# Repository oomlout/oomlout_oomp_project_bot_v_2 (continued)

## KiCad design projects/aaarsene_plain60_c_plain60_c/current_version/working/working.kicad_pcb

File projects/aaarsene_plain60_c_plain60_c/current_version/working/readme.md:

# plain60_c
 
## summary 
* id: aaarsene_plain60_c_plain60_c
* user: aaarsene
* name: plain60_c
* board: plain60_c
* repo: https://github.com/aaarsene/plain60-c
* src_file_repo_kicad_pcb: plain60-c.kicad_pcb
* src_file_repo_kicad_pcb_link: https://github.com/aaarsene/plain60-c/tree/master/plain60-c.kicad_pcb
* src_file_repo_kicad_sch: plain60-c.kicad_sch
* src_file_repo_kicad_sch_link: https://github.com/aaarsene/plain60-c/tree/master/plain60-c.kicad_sch

* src_file_repo_sch: 
* src_file_repo_sch_link: https://github.com/aaarsene/plain60-c/tree/master/
* full details link: https://github.com/oomlout/oomlout_oomp_project_bot_v_2/tree/main/projects/aaarsene_plain60_c_plain60_c/current_version/working  

## schematic  
  
[schematic (pdf)](working_schematic.pdf) 

## pcb  

[board (pdf)](working.pdf)  

## working_bom
| Id | Designator | Footprint | Quantity | Designation | Supplier and ref |  | None | 
| --- | --- | --- | --- | --- | --- | --- | --- | 
| 1 | K19,K20,K23,K24,K17,K22,K21,K18,K8,K10,K14,K5,K13,K12,K11,K9,K7,K6,K4,K2,K1,K3,K62-1,K53,K57,K54,K56,K52,K55,K15-1,K28,K48,K25,K36,K33,K59,K39,K27,K50,K34,K47,K43,K38,K35,K32,K40,K42,K41,K26,K37,K51,K73-1,K49 | CHERRY_PLATE_100H | 53 | KEYSW |  |  | [''] | 
| 2 | K16,K61-1,K29,K63-1,K72-1,K74-1 | CHERRY_PLATE_150H | 6 | KEYSW |  |  | [''] | 
| 3 | K15 | CHERRY_PCB_200H | 1 | KEYSW |  |  | [''] | 
| 4 | K71,K31-1,K46-1,K74,K73,K63,K72,K61,K62 | CHERRY_PLATE_125H | 9 | KEYSW |  |  | [''] | 
| 5 | K58-1,K31 | CHERRY_PLATE_175H | 2 | KEYSW |  |  | [''] | 
| 6 | K44,K46 | CHERRY_PCB_225H | 2 | KEYSW |  |  | [''] | 
| 7 | S4,S5 | 10x5_7x2.5mm | 2 | Screw |  |  | [''] | 
| 8 | K58 | CHERRY_PCB_275H | 1 | KEYSW |  |  | [''] | 
| 9 | K67 | CHERRY_PCB_625H_F | 1 | KEYSW |  |  | [''] | 
| 10 | S8,S7,S9 | 5.5_5x2.5mm | 3 | Tofu screw |  |  | [''] | 
| 11 | S2,S1,S3,S6 | 5.5_5x2.5mm | 4 | Screw |  |  | [''] | 
| 12 | K67-1 | CHERRY_PCB_700H_F | 1 | KEYSW |  |  | [''] | 
| 13 | K44-1 | CHERRY_PCB_200H_V | 1 | KEYSW |  |  | [''] | 
| 14 | D73,D72,D71,D67,D63,D59,D58,D57,D56,D53,D51,D50,D27,D42,D18,D25,D41,D36,D31,D40,D37,D32,D34,D21,D26,D22,D24,D43,D38,D35,D48,D54,D44,D62,D39,D20,D28,D33,D23,D55,D52,D19,D10,D14,D9,D13,D11,D15,D17,D16,D12,D7,D3,D5,D8,D6,D4,D74,D49,D46,D29,D1,D47,D2,D61 | D_0805 | 65 | D |  |  | [''] | 
| 15 | U1 | ATMEGA32U4 | 1 | ATmega32U4 |  |  | [''] | 
| 16 | X1 | Resonator_SMD_muRata_CSTNExxV-3Pin-p1.2 | 1 | XTAL_GND |  |  | [''] | 
| 17 | SW1 | SW_SPST_TL3342 | 1 | SW_PUSH |  |  | [''] | 
| 18 | R6,R5 | R_0805 | 2 | 10k |  |  | [''] | 
| 19 | G*** | oshw | 1 | LOGO |  |  | [''] | 
| 20 | H4 | free_pin | 1 | +5v |  |  | [''] | 
| 21 | H1 | free_pin | 1 | B0 |  |  | [''] | 
| 22 | R1,R2 | R_0805 | 2 | 22 |  |  | [''] | 
| 23 | J1 | HRO-TYPE-C-31-M-12 | 1 | HRO-TYPE-C-31-M-12 |  |  | [''] | 
| 24 | C4,C5,C2,C3 | C_0805 | 4 | 0.1u |  |  | [''] | 
| 25 | F1 | R_0805 | 1 | Polyfuse |  |  | [''] | 
| 26 | C1 | C_0805 | 1 | 1u |  |  | [''] | 
| 27 | R4,R3 | R_0805 | 2 | 5.1k |  |  | [''] | 
| 28 | U2 | USBLC6-2SC6 | 1 | USBLC6-2SC6 |  |  | [''] | 
| 29 | H3 | free_pin | 1 | GND |  |  | [''] | 
| 30 | J2 | isp_standard | 1 | ISP |  |  | [''] | 
| 31 | G*** | logo_new | 1 | LOGO |  |  | [''] | 
| 32 | J3 | JST_SH_SM04B-SRSS-TB_1x04-1MP_P1.00mm_Horizontal | 1 | ai03_ud |  |  | [''] | 
| 33 | LS1 | speaker_AST1109MLTRQ | 1 | Speaker |  |  | [''] | 
| 34 | C6 | C_0805 | 1 | 4.7u |  |  | [''] | 

## bom_schematic
| Ref | Qnty | Value | Cmp name | Footprint | Description | Vendor | DNP | 
| --- | --- | --- | --- | --- | --- | --- | --- | 
| C1 | 1 | 1u | C | Keeb_components:C_0805 | Unpolarized capacitor |  |  | 
| C2, C3, C4, C5 | 4 | 0.1u | C | Keeb_components:C_0805 | Unpolarized capacitor |  |  | 
| C6 | 1 | 4.7u | C | Keeb_components:C_0805 | Unpolarized capacitor |  |  | 
| D1, D2, D3, D4, D5, D6, D7, D8, D9, D10, D11, D12, D13, D14, D15, D16, D17, D18, D19, D20, D21, D22, D23, D24, D25, D26, D27, D28, D29, D31, D32, D33, D34, D35, D36, D37, D38, D39, D40, D41, D42, D43, D44, D46, D47, D48, D49, D50, D51, D52, D53, D54, D55, D56, D57, D58, D59, D61, D62, D63, D67, D71, D72, D73, D74 | 65 | D | D | Keeb_components:D_0805 | Diode |  |  | 
| F1 | 1 | Polyfuse | Polyfuse | Keeb_components:R_0805 | Resettable fuse, polymeric positive temperature coefficient |  |  | 
| H1 | 1 | B0 | Conn_01x01 | footprints:free_pin | Generic connector, single row, 01x01, script generated (kicad-library-utils/schlib/autogen/connector/) |  |  | 
| H3 | 1 | GND | Conn_01x01 | footprints:free_pin | Generic connector, single row, 01x01, script generated (kicad-library-utils/schlib/autogen/connector/) |  |  | 
| H4 | 1 | +5v | Conn_01x01 | footprints:free_pin | Generic connector, single row, 01x01, script generated (kicad-library-utils/schlib/autogen/connector/) |  |  | 
| J1 | 1 | HRO-TYPE-C-31-M-12 | HRO-TYPE-C-31-M-12 | Keeb_components:HRO-TYPE-C-31-M-12 |  |  |  | 
| J2 | 1 | ISP | Conn_02x03_Odd_Even | Keeb_components:isp_standard | Generic connector, double row, 02x03, odd/even pin numbering scheme (row 1 odd numbers, row 2 even numbers), script generated (kicad-library-utils/schlib/autogen/connector/) |  |  | 
| J3 | 1 | ai03_ud | Conn_01x04 | Keeb_components:JST_SH_SM04B-SRSS-TB_1x04-1MP_P1.00mm_Horizontal | Generic connector, single row, 01x04, script generated (kicad-library-utils/schlib/autogen/connector/) |  |  | 
| K1, K2, K3, K4, K5, K6, K7, K8, K9, K10, K11, K12, K13, K14, K17, K18, K19, K20, K21, K22, K23, K24, K25, K26, K27, K28, K32, K33, K34, K35, K36, K37, K38, K39, K40, K41, K42, K43, K47, K48, K49, K50, K51, K52, K53, K54, K55, K56, K57, K59 | 50 | KEYSW | KEYSW | Keeb_switches:CHERRY_PLATE_100H |  |  |  | 
| K15 | 1 | KEYSW | KEYSW | Keeb_switches:CHERRY_PCB_200H |  |  |  | 
| K15-1 | 1 | KEYSW | KEYSW | Keeb_switches:CHERRY_PLATE_100H |  |  |  | 
| K16, K29 | 2 | KEYSW | KEYSW | Keeb_switches:CHERRY_PLATE_150H |  |  |  | 
| K31 | 1 | KEYSW | KEYSW | Keeb_switches:CHERRY_PLATE_175H |  |  |  | 
| K31-1 | 1 | KEYSW | KEYSW | Keeb_switches:CHERRY_PLATE_125H |  |  |  | 
| K44, K46 | 2 | KEYSW | KEYSW | Keeb_switches:CHERRY_PCB_225H |  |  |  | 
| K44-1 | 1 | KEYSW | KEYSW | Keeb_switches:CHERRY_PCB_200H_V |  |  |  | 
| K46-1 | 1 | KEYSW | KEYSW | Keeb_switches:CHERRY_PLATE_125H |  |  |  | 
| K58 | 1 | KEYSW | KEYSW | Keeb_switches:CHERRY_PCB_275H |  |  |  | 
| K58-1 | 1 | KEYSW | KEYSW | Keeb_switches:CHERRY_PLATE_175H |  |  |  | 
| K61, K62, K63, K71, K72, K73, K74 | 7 | KEYSW | KEYSW | Keeb_switches:CHERRY_PLATE_125H |  |  |  | 
| K61-1 | 1 | KEYSW | KEYSW | Keeb_switches:CHERRY_PLATE_150H |  |  |  | 
| K62-1 | 1 | KEYSW | KEYSW | Keeb_switches:CHERRY_PLATE_100H |  |  |  | 
| K63-1 | 1 | KEYSW | KEYSW | Keeb_switches:CHERRY_PLATE_150H |  |  |  | 
| K67 | 1 | KEYSW | KEYSW | Keeb_switches:CHERRY_PCB_625H_F |  |  |  | 
| K67-1 | 1 | KEYSW | KEYSW | Keeb_switches:CHERRY_PCB_700H_F |  |  |  | 
| K72-1 | 1 | KEYSW | KEYSW | Keeb_switches:CHERRY_PLATE_150H |  |  |  | 
| K73-1 | 1 | KEYSW | KEYSW | Keeb_switches:CHERRY_PLATE_100H |  |  |  | 
| K74-1 | 1 | KEYSW | KEYSW | Keeb_switches:CHERRY_PLATE_150H |  |  |  | 
| LS1 | 1 | Speaker | Speaker | Keeb_components:speaker_AST1109MLTRQ | Speaker |  |  | 
| R1, R2 | 2 | 22 | R | Keeb_components:R_0805 | Resistor |  |  | 
| R3, R4 | 2 | 5.1k | R | Keeb_components:R_0805 | Resistor |  |  | 
| R5, R6 | 2 | 10k | R | Keeb_components:R_0805 | Resistor |  |  | 
| S1, S2, S3, S6 | 4 | Screw | Screw_Terminal_01x01 | footprints:5.5_5x2.5mm | Generic screw terminal, single row, 01x01, script generated (kicad-library-utils/schlib/autogen/connector/) |  |  | 
| S4, S5 | 2 | Screw | Screw_Terminal_01x01 | footprints:10x5_7x2.5mm | Generic screw terminal, single row, 01x01, script generated (kicad-library-utils/schlib/autogen/connector/) |  |  | 
| S7, S8, S9 | 3 | Tofu screw | Screw_Terminal_01x01 | footprints:5.5_5x2.5mm | Generic screw terminal, single row, 01x01, script generated (kicad-library-utils/schlib/autogen/connector/) |  |  | 
| SW1 | 1 | SW_PUSH | SW_PUSH | Button_Switch_SMD:SW_SPST_TL3342 |  |  |  | 
| U1 | 1 | ATmega32U4 | ATmega32U4 | Keeb_components:ATMEGA32U4 |  |  |  | 
| U2 | 1 | USBLC6-2SC6 | USBLC6-2SC6 | Keeb_components:USBLC6-2SC6 |  |  |  | 
| X1 | 1 | XTAL_GND | XTAL_GND | Keeb_components:Resonator_SMD_muRata_CSTNExxV-3Pin-p1.2 |  |  |  |

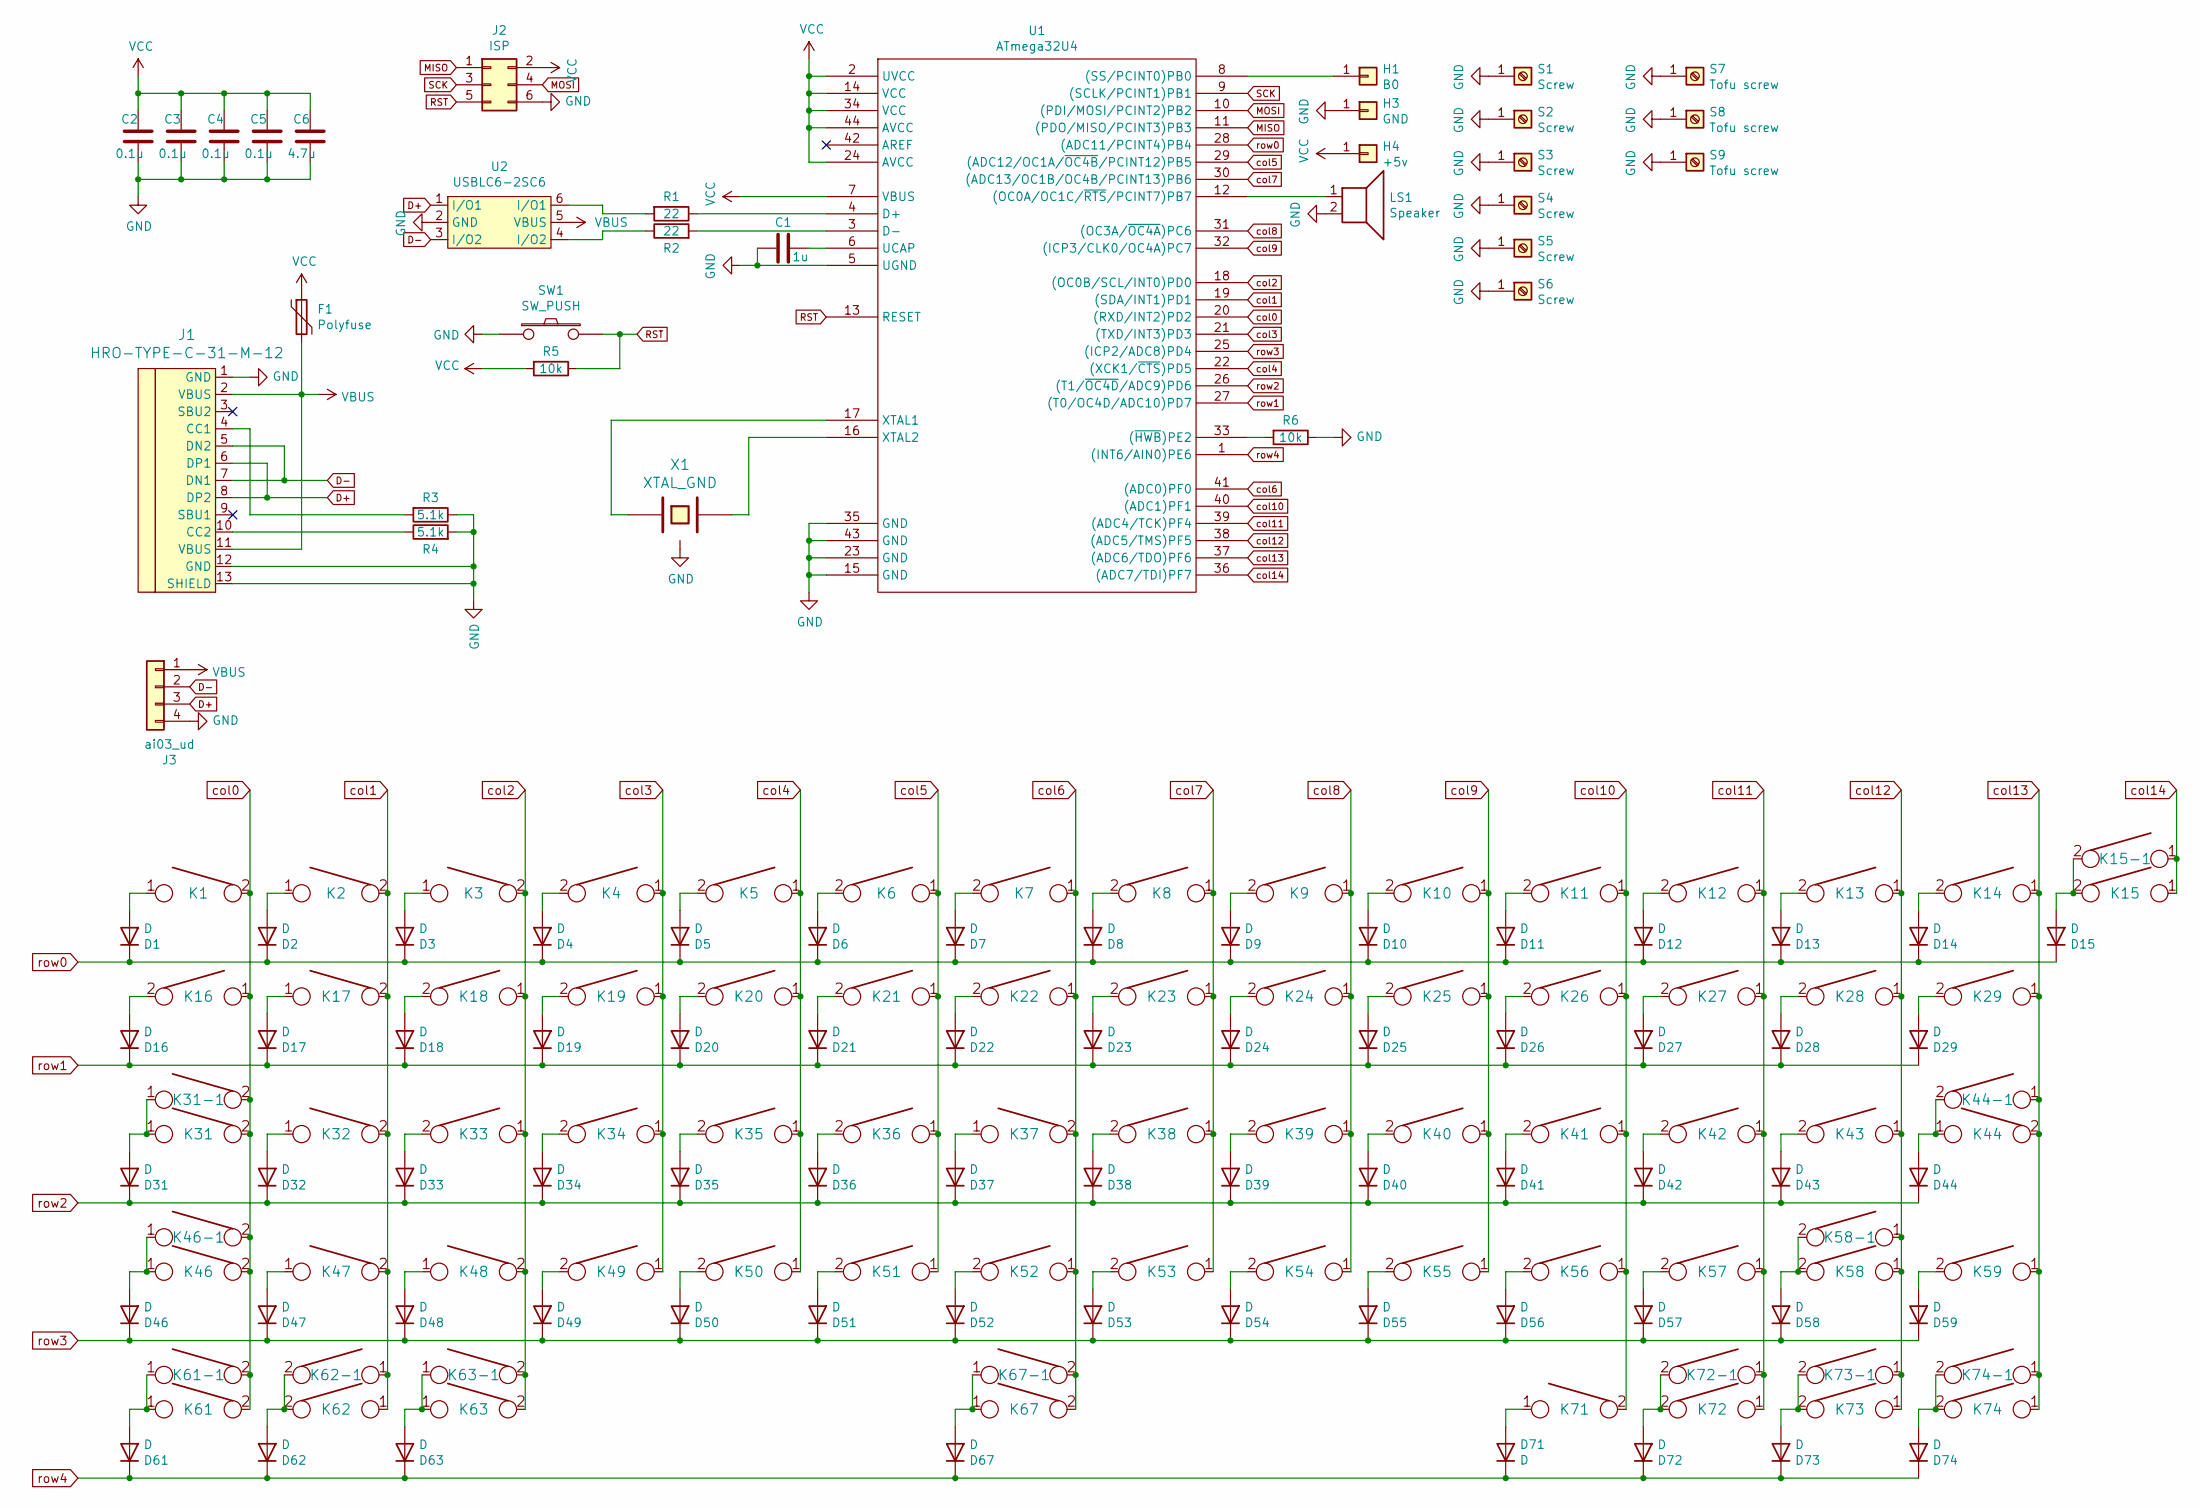
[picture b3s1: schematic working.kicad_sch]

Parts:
C1: 1u; C_0805
C2, C3, C4, C5: 0.1u; C_0805
C6: 4.7u; C_0805
D1, D2, D3, D4, D5, D6, D7, D8, D9, D10, D11, D12, D13, D14, D15, D16, D17, D18, D19, D20, D21, D22, D23, D24, D25, D26, D27, D28, D29, D31, D32, D33, D34, D35, D36, D37, D38, D39, D40, D41, D42, D43, D44, D46, D47, D48, D49, D50, D51, D52, D53, D54, D55, D56, D57, D58, D59, D61, D62, D63, D67, D71, D72, D73, D74: D; D_0805
F1: Polyfuse; R_0805
H1: B0; free_pin
H3: GND; free_pin
H4: +5v; free_pin
J1: HRO-TYPE-C-31-M-12
J2: ISP; isp_standard
J3: ai03_ud; JST_SH_SM04B-SRSS-TB_1x04-1MP_P1.00mm_Horizontal
K1, K2, K3, K4, K5, K6, K7, K8, K9, K10, K11, K12, K13, K14, K15-1, K17, K18, K19, K20, K21, K22, K23, K24, K25, K26, K27, K28, K32, K33, K34, K35, K36, K37, K38, K39, K40, K41, K42, K43, K47, K48, K49, K50, K51, K52, K53, K54, K55, K56, K57, K59, K62-1, K73-1: KEYSW; CHERRY_PLATE_100H
K15: KEYSW; CHERRY_PCB_200H
K16, K29, K61-1, K63-1, K72-1, K74-1: KEYSW; CHERRY_PLATE_150H
K31, K58-1: KEYSW; CHERRY_PLATE_175H
K31-1, K46-1, K61, K62, K63, K71, K72, K73, K74: KEYSW; CHERRY_PLATE_125H
K44, K46: KEYSW; CHERRY_PCB_225H
K44-1: KEYSW; CHERRY_PCB_200H_V
K58: KEYSW; CHERRY_PCB_275H
K67: KEYSW; CHERRY_PCB_625H_F
K67-1: KEYSW; CHERRY_PCB_700H_F
LS1: Speaker; speaker_AST1109MLTRQ
R1, R2: 22; R_0805
R3, R4: 5.1k; R_0805
R5, R6: 10k; R_0805
S1, S2, S3, S6: Screw; 5.5_5x2.5mm
S4, S5: Screw; 10x5_7x2.5mm
S7, S8, S9: Tofu screw; 5.5_5x2.5mm
SW1: SW_PUSH; SW_SPST_TL3342
U1: ATmega32U4; ATMEGA32U4
U2: USBLC6-2SC6; Farnell 1295310
X1: XTAL_GND; Resonator_SMD_muRata_CSTNExxV-3Pin-p1.2

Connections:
D+: J1.6 (DP1), J1.8 (DP2), J3.3, U2.1 (I/O1)
D-: J1.5 (DN2), J1.7 (DN1), J3.2, U2.3 (I/O2)
GND: C1.2, C2.1, C3.1, C4.1, C5.1, C6.1, H3.1, J1.1 (GND), J1.12 (GND), J1.13 (SHIELD), J2.6, J3.4, LS1.2, R3.1, R4.2, R6.1, S1.1, S2.1, S3.1, S4.1, S5.1, S6.1, S7.1, S8.1, S9.1, SW1.1, U1.5 (UGND), U1.15 (GND), U1.23 (GND), U1.35 (GND), U1.43 (GND), U2.2 (GND), X1.3
MISO: J2.1, U1.11 ((PDO/MISO/PCINT3)PB3)
MOSI: J2.4, U1.10 ((PDI/MOSI/PCINT2)PB2)
unnamed: C1.1, U1.6 (UCAP)
unnamed: D1.2 (A), K1.1
unnamed: D2.2 (A), K2.1
unnamed: D3.2 (A), K3.1
unnamed: D4.2 (A), K4.2
unnamed: D5.2 (A), K5.2
unnamed: D6.2 (A), K6.2
unnamed: D7.2 (A), K7.2
unnamed: D8.2 (A), K8.2
unnamed: D9.2 (A), K9.2
unnamed: D10.2 (A), K10.2
unnamed: D11.2 (A), K11.2
unnamed: D12.2 (A), K12.2
unnamed: D13.2 (A), K13.2
unnamed: D14.2 (A), K14.2
unnamed: D15.2 (A), K15.2, K15-1.2
unnamed: D16.2 (A), K16.2
unnamed: D17.2 (A), K17.1
unnamed: D18.2 (A), K18.2
unnamed: D19.2 (A), K19.2
unnamed: D20.2 (A), K20.2
unnamed: D21.2 (A), K21.2
unnamed: D22.2 (A), K22.2
unnamed: D23.2 (A), K23.2
unnamed: D24.2 (A), K24.2
unnamed: D25.2 (A), K25.2
unnamed: D26.2 (A), K26.2
unnamed: D27.2 (A), K27.2
unnamed: D28.2 (A), K28.2
unnamed: D29.2 (A), K29.2
unnamed: D31.2 (A), K31.1, K31-1.1
unnamed: D32.2 (A), K32.1
unnamed: D33.2 (A), K33.2
unnamed: D34.2 (A), K34.2
unnamed: D35.2 (A), K35.2
unnamed: D36.2 (A), K36.2
unnamed: D37.2 (A), K37.1
unnamed: D38.2 (A), K38.2
unnamed: D39.2 (A), K39.2
unnamed: D40.2 (A), K40.2
unnamed: D41.2 (A), K41.2
unnamed: D42.2 (A), K42.2
unnamed: D43.2 (A), K43.2
unnamed: D44.2 (A), K44.1, K44-1.2
unnamed: D46.2 (A), K46.1, K46-1.1
unnamed: D47.2 (A), K47.1
unnamed: D48.2 (A), K48.1
unnamed: D49.2 (A), K49.2
unnamed: D50.2 (A), K50.2
unnamed: D51.2 (A), K51.2
unnamed: D52.2 (A), K52.2
unnamed: D53.2 (A), K53.2
unnamed: D54.2 (A), K54.2
unnamed: D55.2 (A), K55.2
unnamed: D56.2 (A), K56.2
unnamed: D57.2 (A), K57.2
unnamed: D58.2 (A), K58.2, K58-1.2
unnamed: D59.2 (A), K59.2
unnamed: D61.2 (A), K61.1, K61-1.1
unnamed: D62.2 (A), K62.2, K62-1.2
unnamed: D63.2 (A), K63.1, K63-1.1
unnamed: D67.2 (A), K67.1, K67-1.1
unnamed: D71.2 (A), K71.1
unnamed: D72.2 (A), K72.2, K72-1.2
unnamed: D73.2 (A), K73.2, K73-1.2
unnamed: D74.2 (A), K74.2, K74-1.2
unnamed: H1.1, U1.8 ((SS/PCINT0)PB0)
unnamed: J1.4 (CC1), R3.2
unnamed: J1.10 (CC2), R4.1
unnamed: LS1.1, U1.12 ((OC0A/OC1C/~RTS~/PCINT7)PB7)
unnamed: R1.1, U1.4 (D+)
unnamed: R1.2, U2.6 (I/O1)
unnamed: R2.1, U2.4 (I/O2)
unnamed: R2.2, U1.3 (D-)
unnamed: R6.2, U1.33 ((~HWB~)PE2)
unnamed: U1.16 (XTAL2), X1.2
unnamed: U1.17 (XTAL1), X1.1
RST: J2.5, R5.1, SW1.2, U1.13 (RESET)
SCK: J2.3, U1.9 ((SCLK/PCINT1)PB1)
VBUS: F1.2, J1.2 (VBUS), J1.11 (VBUS), J3.1, U2.5 (VBUS)
VCC: C2.2, C3.2, C4.2, C5.2, C6.2, F1.1, H4.1, J2.2, R5.2, U1.2 (UVCC), U1.7 (VBUS), U1.14 (VCC), U1.24 (AVCC), U1.34 (VCC), U1.44 (AVCC)
col0: K1.2, K16.1, K31.2, K31-1.2, K46.2, K46-1.2, K61.2, K61-1.2, U1.20 ((RXD/INT2)PD2)
col1: K2.2, K17.2, K32.2, K47.2, K62.1, K62-1.1, U1.19 ((SDA/INT1)PD1)
col2: K3.2, K18.1, K33.1, K48.2, K63.2, K63-1.2, U1.18 ((OC0B/SCL/INT0)PD0)
col3: K4.1, K19.1, K34.1, K49.1, U1.21 ((TXD/INT3)PD3)
col4: K5.1, K20.1, K35.1, K50.1, U1.22 ((XCK1/~CTS~)PD5)
col5: K6.1, K21.1, K36.1, K51.1, U1.29 ((ADC12/OC1A/~OC4B~/PCINT12)PB5)
col6: K7.1, K22.1, K37.2, K52.1, K67.2, K67-1.2, U1.41 ((ADC0)PF0)
col7: K8.1, K23.1, K38.1, K53.1, U1.30 ((ADC13/OC1B/OC4B/PCINT13)PB6)
col8: K9.1, K24.1, K39.1, K54.1, U1.31 ((OC3A/~OC4A~)PC6)
col9: K10.1, K25.1, K40.1, K55.1, U1.32 ((ICP3/CLK0/OC4A)PC7)
col10: K11.1, K26.1, K41.1, K56.1, K71.2, U1.40 ((ADC1)PF1)
col11: K12.1, K27.1, K42.1, K57.1, K72.1, K72-1.1, U1.39 ((ADC4/TCK)PF4)
col12: K13.1, K28.1, K43.1, K58.1, K58-1.1, K73.1, K73-1.1, U1.38 ((ADC5/TMS)PF5)
col13: K14.1, K29.1, K44.2, K44-1.1, K59.1, K74.1, K74-1.1, U1.37 ((ADC6/TDO)PF6)
col14: K15.1, K15-1.1, U1.36 ((ADC7/TDI)PF7)
row0: D1.1 (K), D2.1 (K), D3.1 (K), D4.1 (K), D5.1 (K), D6.1 (K), D7.1 (K), D8.1 (K), D9.1 (K), D10.1 (K), D11.1 (K), D12.1 (K), D13.1 (K), D14.1 (K), D15.1 (K), U1.28 ((ADC11/PCINT4)PB4)
row1: D16.1 (K), D17.1 (K), D18.1 (K), D19.1 (K), D20.1 (K), D21.1 (K), D22.1 (K), D23.1 (K), D24.1 (K), D25.1 (K), D26.1 (K), D27.1 (K), D28.1 (K), D29.1 (K), U1.27 ((T0/OC4D/ADC10)PD7)
row2: D31.1 (K), D32.1 (K), D33.1 (K), D34.1 (K), D35.1 (K), D36.1 (K), D37.1 (K), D38.1 (K), D39.1 (K), D40.1 (K), D41.1 (K), D42.1 (K), D43.1 (K), D44.1 (K), U1.26 ((T1/~OC4D~/ADC9)PD6)
row3: D46.1 (K), D47.1 (K), D48.1 (K), D49.1 (K), D50.1 (K), D51.1 (K), D52.1 (K), D53.1 (K), D54.1 (K), D55.1 (K), D56.1 (K), D57.1 (K), D58.1 (K), D59.1 (K), U1.25 ((ICP2/ADC8)PD4)
row4: D61.1 (K), D62.1 (K), D63.1 (K), D67.1 (K), D71.1 (K), D72.1 (K), D73.1 (K), D74.1 (K), U1.1 ((INT6/AIN0)PE6)

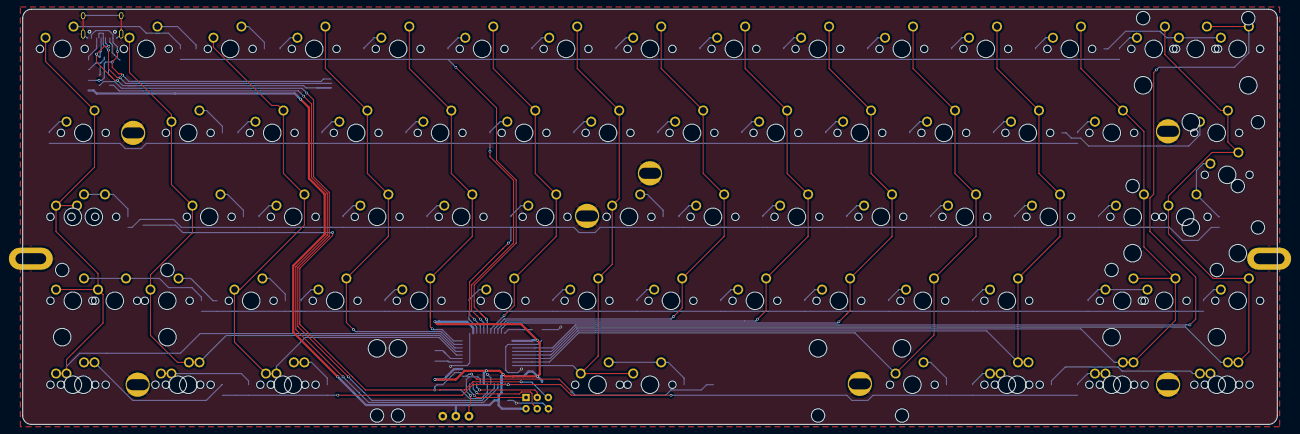
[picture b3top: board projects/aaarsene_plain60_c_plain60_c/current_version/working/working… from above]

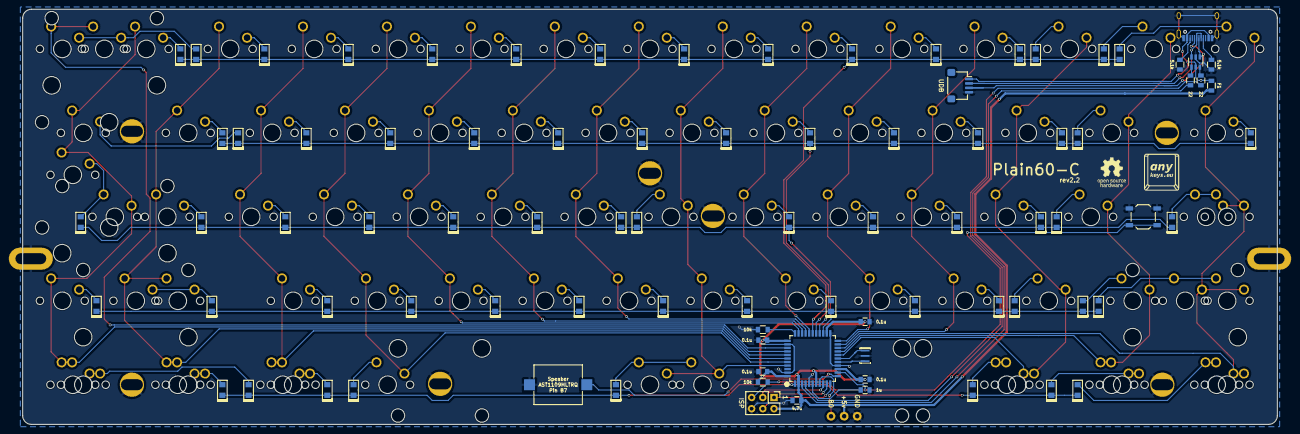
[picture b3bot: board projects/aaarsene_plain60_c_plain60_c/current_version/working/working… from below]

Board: 2 copper layers, 284.7 x 94.2 mm, 175 parts (89 on the bottom side), 106 nets.

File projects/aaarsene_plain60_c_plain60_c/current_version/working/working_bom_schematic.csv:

"Source:","C:\gh\oomlout_oomp_project_bot_v_2\projects\aaarsene_plain60_c_plain60_c\current_version\working\working.kicad_sch"
"Date:","13/09/2023 15:20:31"
"Tool:","Eeschema 7.0.6"
"Generator:","C:/Program Files/KiCad/7.0/bin/scripting/plugins/bom_csv_grouped_by_value_with_fp.py"
"Component Count:","175"
"Ref","Qnty","Value","Cmp name","Footprint","Description","Vendor","DNP"
"C1","1","1u","C","Keeb_components:C_0805","Unpolarized capacitor","",""
"C2, C3, C4, C5","4","0.1u","C","Keeb_components:C_0805","Unpolarized capacitor","",""
"C6","1","4.7u","C","Keeb_components:C_0805","Unpolarized capacitor","",""
"D1, D2, D3, D4, D5, D6, D7, D8, D9, D10, D11, D12, D13, D14, D15, D16, D17, D18, D19, D20, D21, D22, D23, D24, D25, D26, D27, D28, D29, D31, D32, D33, D34, D35, D36, D37, D38, D39, D40, D41, D42, D43, D44, D46, D47, D48, D49, D50, D51, D52, D53, D54, D55, D56, D57, D58, D59, D61, D62, D63, D67, D71, D72, D73, D74","65","D","D","Keeb_components:D_0805","Diode","",""
"F1","1","Polyfuse","Polyfuse","Keeb_components:R_0805","Resettable fuse, polymeric positive temperature coefficient","",""
"H1","1","B0","Conn_01x01","footprints:free_pin","Generic connector, single row, 01x01, script generated (kicad-library-utils/schlib/autogen/connector/)","",""
"H3","1","GND","Conn_01x01","footprints:free_pin","Generic connector, single row, 01x01, script generated (kicad-library-utils/schlib/autogen/connector/)","",""
"H4","1","+5v","Conn_01x01","footprints:free_pin","Generic connector, single row, 01x01, script generated (kicad-library-utils/schlib/autogen/connector/)","",""
"J1","1","HRO-TYPE-C-31-M-12","HRO-TYPE-C-31-M-12","Keeb_components:HRO-TYPE-C-31-M-12","","",""
"J2","1","ISP","Conn_02x03_Odd_Even","Keeb_components:isp_standard","Generic connector, double row, 02x03, odd/even pin numbering scheme (row 1 odd numbers, row 2 even numbers), script generated (kicad-library-utils/schlib/autogen/connector/)","",""
"J3","1","ai03_ud","Conn_01x04","Keeb_components:JST_SH_SM04B-SRSS-TB_1x04-1MP_P1.00mm_Horizontal","Generic connector, single row, 01x04, script generated (kicad-library-utils/schlib/autogen/connector/)","",""
"K1, K2, K3, K4, K5, K6, K7, K8, K9, K10, K11, K12, K13, K14, K17, K18, K19, K20, K21, K22, K23, K24, K25, K26, K27, K28, K32, K33, K34, K35, K36, K37, K38, K39, K40, K41, K42, K43, K47, K48, K49, K50, K51, K52, K53, K54, K55, K56, K57, K59","50","KEYSW","KEYSW","Keeb_switches:CHERRY_PLATE_100H","","",""
"K15","1","KEYSW","KEYSW","Keeb_switches:CHERRY_PCB_200H","","",""
"K15-1","1","KEYSW","KEYSW","Keeb_switches:CHERRY_PLATE_100H","","",""
"K16, K29","2","KEYSW","KEYSW","Keeb_switches:CHERRY_PLATE_150H","","",""
"K31","1","KEYSW","KEYSW","Keeb_switches:CHERRY_PLATE_175H","","",""
"K31-1","1","KEYSW","KEYSW","Keeb_switches:CHERRY_PLATE_125H","","",""
"K44, K46","2","KEYSW","KEYSW","Keeb_switches:CHERRY_PCB_225H","","",""
"K44-1","1","KEYSW","KEYSW","Keeb_switches:CHERRY_PCB_200H_V","","",""
"K46-1","1","KEYSW","KEYSW","Keeb_switches:CHERRY_PLATE_125H","","",""
"K58","1","KEYSW","KEYSW","Keeb_switches:CHERRY_PCB_275H","","",""
"K58-1","1","KEYSW","KEYSW","Keeb_switches:CHERRY_PLATE_175H","","",""
"K61, K62, K63, K71, K72, K73, K74","7","KEYSW","KEYSW","Keeb_switches:CHERRY_PLATE_125H","","",""
"K61-1","1","KEYSW","KEYSW","Keeb_switches:CHERRY_PLATE_150H","","",""
"K62-1","1","KEYSW","KEYSW","Keeb_switches:CHERRY_PLATE_100H","","",""
"K63-1","1","KEYSW","KEYSW","Keeb_switches:CHERRY_PLATE_150H","","",""
"K67","1","KEYSW","KEYSW","Keeb_switches:CHERRY_PCB_625H_F","","",""
"K67-1","1","KEYSW","KEYSW","Keeb_switches:CHERRY_PCB_700H_F","","",""
"K72-1","1","KEYSW","KEYSW","Keeb_switches:CHERRY_PLATE_150H","","",""
"K73-1","1","KEYSW","KEYSW","Keeb_switches:CHERRY_PLATE_100H","","",""
"K74-1","1","KEYSW","KEYSW","Keeb_switches:CHERRY_PLATE_150H","","",""
"LS1","1","Speaker","Speaker","Keeb_components:speaker_AST1109MLTRQ","Speaker","",""
"R1, R2","2","22","R","Keeb_components:R_0805","Resistor","",""
"R3, R4","2","5.1k","R","Keeb_components:R_0805","Resistor","",""
"R5, R6","2","10k","R","Keeb_components:R_0805","Resistor","",""
"S1, S2, S3, S6","4","Screw","Screw_Terminal_01x01","footprints:5.5_5x2.5mm","Generic screw terminal, single row, 01x01, script generated (kicad-library-utils/schlib/autogen/connector/)","",""
"S4, S5","2","Screw","Screw_Terminal_01x01","footprints:10x5_7x2.5mm","Generic screw terminal, single row, 01x01, script generated (kicad-library-utils/schlib/autogen/connector/)","",""
"S7, S8, S9","3","Tofu screw","Screw_Terminal_01x01","footprints:5.5_5x2.5mm","Generic screw terminal, single row, 01x01, script generated (kicad-library-utils/schlib/autogen/connector/)","",""
"SW1","1","SW_PUSH","SW_PUSH","Button_Switch_SMD:SW_SPST_TL3342","","",""
"U1","1","ATmega32U4","ATmega32U4","Keeb_components:ATMEGA32U4","","",""
"U2","1","USBLC6-2SC6","USBLC6-2SC6","Keeb_components:USBLC6-2SC6","","",""
"X1","1","XTAL_GND","XTAL_GND","Keeb_components:Resonator_SMD_muRata_CSTNExxV-3Pin-p1.2","","",""

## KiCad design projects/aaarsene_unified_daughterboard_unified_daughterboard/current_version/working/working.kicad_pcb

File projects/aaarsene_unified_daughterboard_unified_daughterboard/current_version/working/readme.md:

# unified_daughterboard
 
## summary 
* id: aaarsene_unified_daughterboard_unified_daughterboard
* user: aaarsene
* name: unified_daughterboard
* board: unified_daughterboard
* repo: https://github.com/aaarsene/Unified-Daughterboard
* src_file_repo_kicad_pcb: KiCad/C3/Unified-Daughterboard.kicad_pcb
* src_file_repo_kicad_pcb_link: https://github.com/aaarsene/Unified-Daughterboard/tree/master/KiCad/C3/Unified-Daughterboard.kicad_pcb

* src_file_repo_sch: KiCad/C3/Unified-Daughterboard.sch
* src_file_repo_sch_link: https://github.com/aaarsene/Unified-Daughterboard/tree/master/KiCad/C3/Unified-Daughterboard.sch
* full details link: https://github.com/oomlout/oomlout_oomp_project_bot_v_2/tree/main/projects/aaarsene_unified_daughterboard_unified_daughterboard/current_version/working  

## schematic  
  
[schematic (pdf)](working_schematic.pdf) 

## pcb  

[board (pdf)](working.pdf)  

## working_bom
| Id | Designator | Footprint | Quantity | Designation | Supplier and ref |  | None | 
| --- | --- | --- | --- | --- | --- | --- | --- | 
| 1 | J1 | TYPE-C-31-M-12 | 1 | TYPE-C-31-M12_13 |  |  | [''] | 
| 2 | J2 | JST-SR-4 | 1 | SM04B-SRSS-TB(LF)(SN) |  |  | [''] | 
| 3 | D1 | D_SOD-123_Bidirectional | 1 | SMF9.0CA |  |  | [''] | 
| 4 | F1 | Fuse_1206_3216Metric | 1 | ASMD1206-150 |  |  | [''] | 
| 5 | U1 | USON-10_2.5x1.0mm_P0.5mm | 1 | TPD4E05U06DQAR |  |  | [''] | 
| 6 | R2,R1 | R_0603 | 2 | 5.1k |  |  | [''] | 
| 7 | L1 | L_1206_3216Metric | 1 | 60R@100MHz |  |  | [''] | 
| 8 | G2 | Unified-Daughterboard-Name.pretty | 1 | Unified-Daughterboard-Name |  |  | [''] | 
| 9 | G1 | Unified-Daughterboard-Logo.pretty | 1 | Unified-Daughterboard-Logo |  |  | [''] | 

## bom_schematic
| Ref | Qnty | Value | Cmp name | Footprint | Description | Vendor | DNP | 
| --- | --- | --- | --- | --- | --- | --- | --- | 
| D1 | 1 | SMF9.0CA | D_TVS | acheron_Components:D_SOD-123_Bidirectional | Bidirectional transient-voltage-suppression diode |  |  | 
| F1 | 1 | ASMD1206-150 | Polyfuse | Fuse:Fuse_1206_3216Metric | Resettable fuse, polymeric positive temperature coefficient |  |  | 
| G1 | 1 | Unified-Daughterboard-Logo | MountingHole | Unified-Daughterboard-Logo:Unified-Daughterboard-Logo.pretty | Mounting Hole without connection |  |  | 
| G2 | 1 | Unified-Daughterboard-Name | MountingHole | Unified-Daughterboard-Logo:Unified-Daughterboard-Name.pretty | Mounting Hole without connection |  |  | 
| J1 | 1 | TYPE-C-31-M12_13 | TYPE-C-31-M12_13-acheronSymbols | acheron_Connectors:TYPE-C-31-M-12 |  |  |  | 
| J2 | 1 | SM04B-SRSS-TB(LF)(SN) | Conn_01x04 | random-keyboard-parts:JST-SR-4 | Generic connector, single row, 01x04, script generated (kicad-library-utils/schlib/autogen/connector/) |  |  | 
| L1 | 1 | 60R@100MHz | L_Core_Ferrite-Device | Inductor_SMD:L_1206_3216Metric |  |  |  | 
| MH1, MH2, MH3, MH4 | 4 | Mount-M2 | Conn_01x01 | random-keyboard-parts:Generic-Mounthole | Generic connector, single row, 01x01, script generated (kicad-library-utils/schlib/autogen/connector/) |  |  | 
| R1, R2 | 2 | 5.1k | R_Small | Resistors_SMD:R_0603 | Resistor, small symbol |  |  | 
| U1 | 1 | TPD4E05U06DQAR | TPD4E05U06DQAR-acheronSymbols | acheron_Components:USON-10_2.5x1.0mm_P0.5mm |  |  |  |

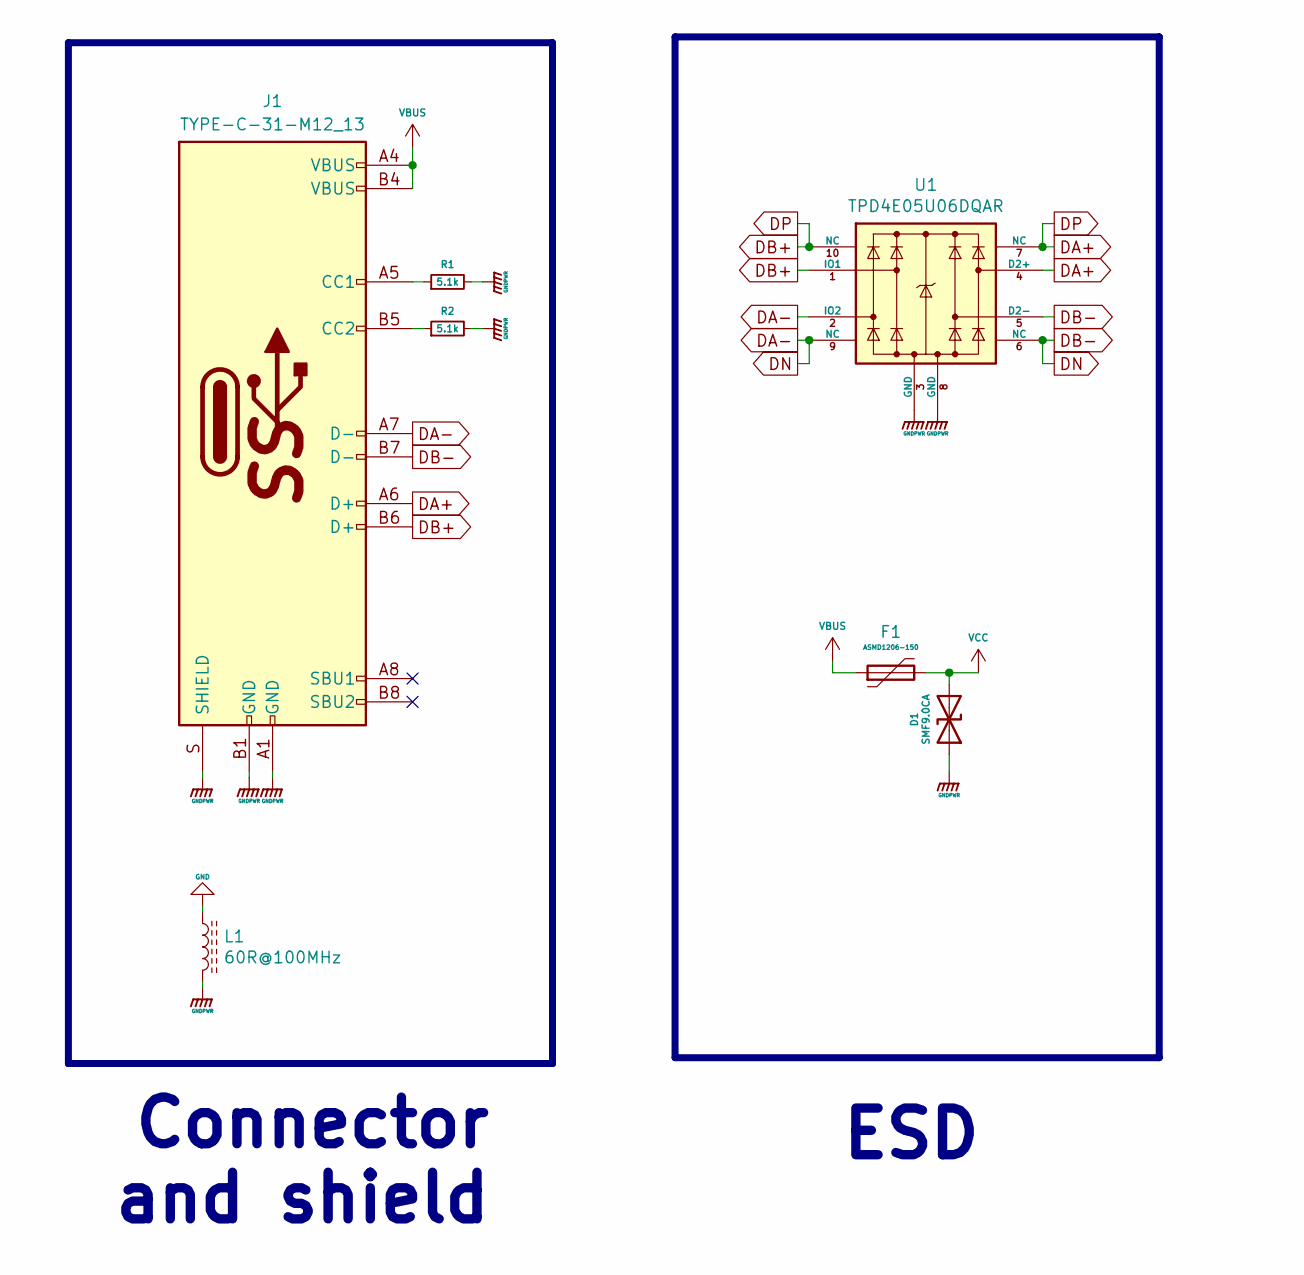
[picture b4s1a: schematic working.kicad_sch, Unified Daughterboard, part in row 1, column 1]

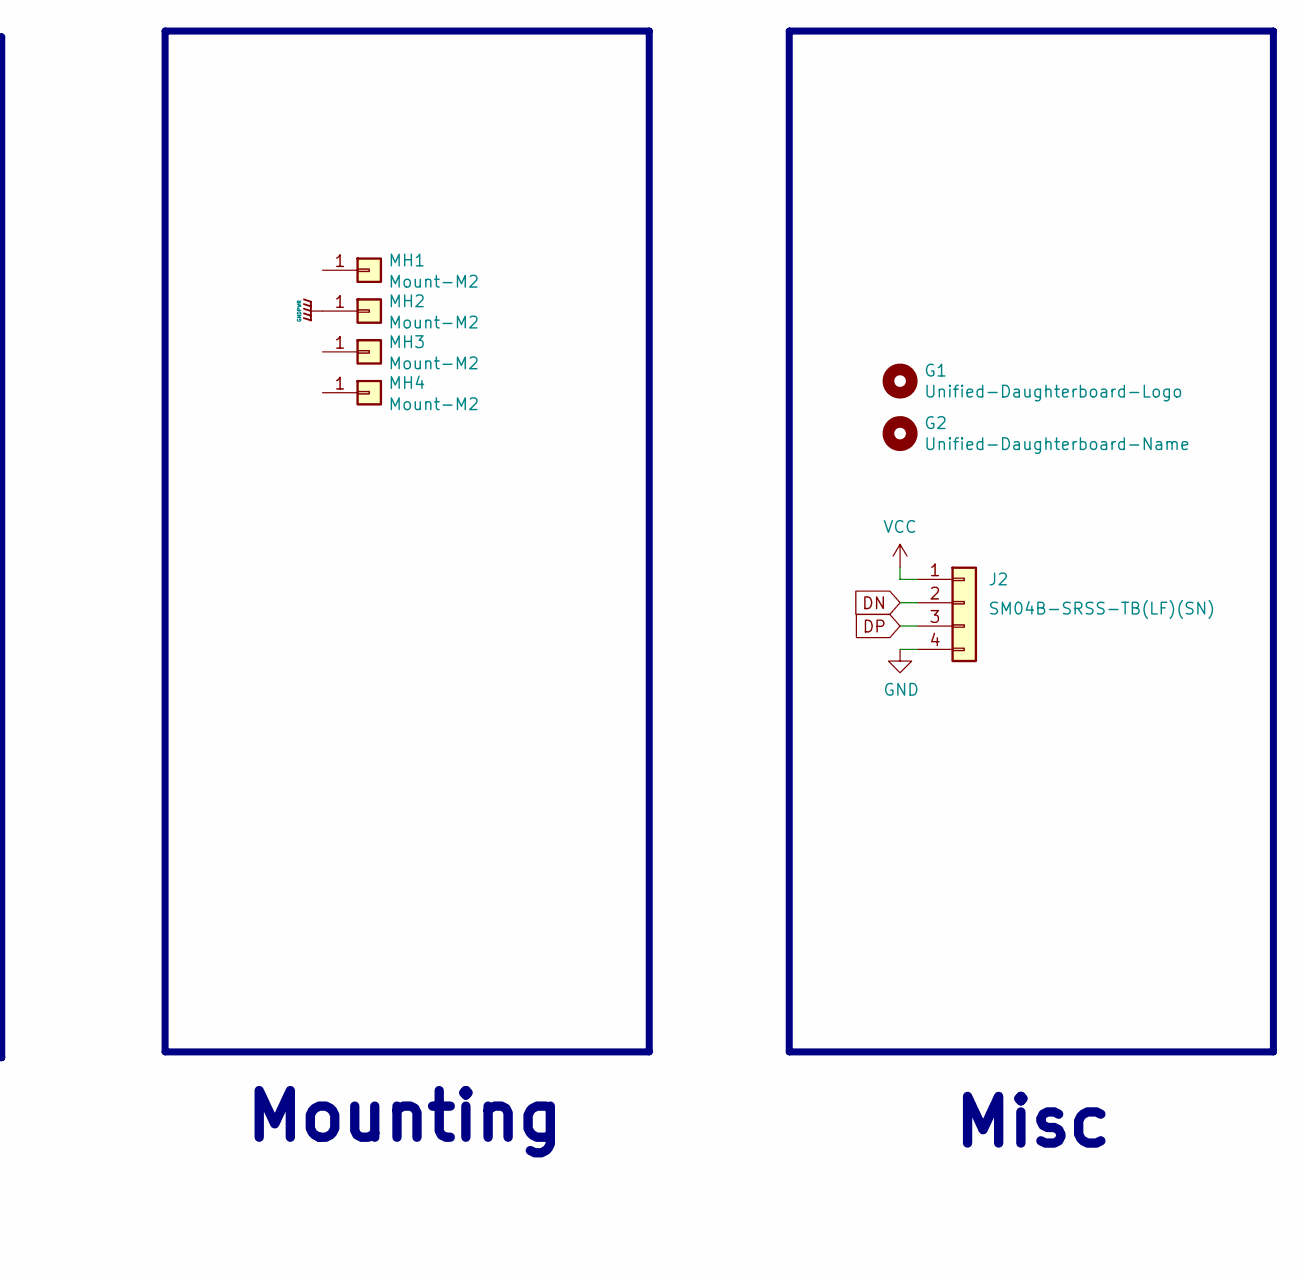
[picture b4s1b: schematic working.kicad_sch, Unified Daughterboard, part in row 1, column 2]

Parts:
D1: SMF9.0CA; D_SOD-123_Bidirectional; Manufacturer Part No SMF9.0CA; LCSC Part No C123799
F1: ASMD1206-150; Fuse_1206_3216Metric; Manufacturer Part No ASMD1206-150; LCSC Part No C135342
G1: Unified-Daughterboard-Logo; Unified-Daughterboard-Logo.pretty
G2: Unified-Daughterboard-Name; Unified-Daughterboard-Name.pretty
J1: TYPE-C-31-M12_13; TYPE-C-31-M-12; Manufacturer Part No TYPE-C-31-M-12; LCSC Part No C165948
J2: SM04B-SRSS-TB(LF)(SN); JST-SR-4; Manufacturer Part No SM04B-SRSS-TB(LF)(SN); LCSC Part No C160404
L1: 60R@100MHz; L_1206_3216Metric; Manufacturer Part No MLB3216-600P4A(f); LCSC Part No C33600
MH1, MH2, MH3, MH4: Mount-M2; Generic-Mounthole
R1, R2: 5.1k; R_0603
U1: TPD4E05U06DQAR; USON-10_2.5x1.0mm_P0.5mm; Manufacturer Part No TPD4E05U06DQAR; LCSC Part No C138714

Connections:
DA+: J1.A6 (D+), J1.B6 (D+), J2.3, U1.1 (IO1), U1.4 (D2+), U1.7 (NC), U1.10 (NC)
DA-: J1.A7 (D-), J1.B7 (D-), J2.2, U1.2 (IO2), U1.5 (D2-), U1.6 (NC), U1.9 (NC)
GND: J2.4, L1.1
GNDPWR: D1.1 (A1), J1.A1 (GND), J1.B1 (GND), J1.S (SHIELD), L1.2, MH2.1, R1.2, R2.2, U1.3 (GND), U1.8 (GND)
unnamed: J1.A5 (CC1), R1.1
unnamed: J1.B5 (CC2), R2.1
VBUS: F1.1, J1.A4 (VBUS), J1.B4 (VBUS)
VCC: D1.2 (A2), F1.2, J2.1

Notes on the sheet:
Misc
Mounting
Connector and shield
ESD

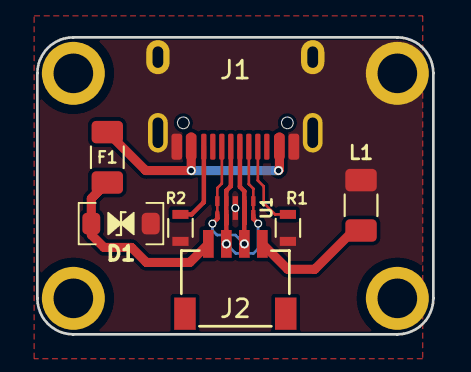
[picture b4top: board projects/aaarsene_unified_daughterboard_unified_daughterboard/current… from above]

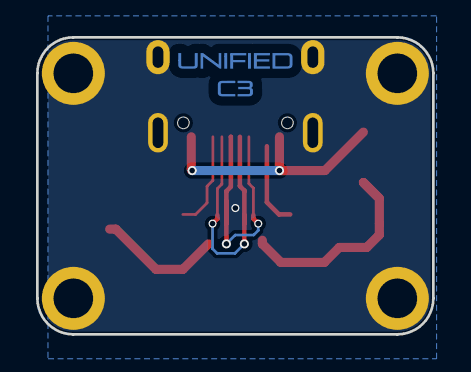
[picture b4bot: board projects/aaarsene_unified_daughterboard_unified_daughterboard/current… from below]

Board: 2 copper layers, 22.0 x 16.5 mm, 14 parts (2 on the bottom side), 8 nets.

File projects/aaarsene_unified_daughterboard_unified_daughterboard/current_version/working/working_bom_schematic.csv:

"Source:","C:\gh\oomlout_oomp_project_bot_v_2\projects\aaarsene_unified_daughterboard_unified_daughterboard\current_version\working\working.kicad_sch"
"Date:","13/09/2023 15:44:00"
"Tool:","Eeschema 7.0.6"
"Generator:","C:/Program Files/KiCad/7.0/bin/scripting/plugins/bom_csv_grouped_by_value_with_fp.py"
"Component Count:","14"
"Ref","Qnty","Value","Cmp name","Footprint","Description","Vendor","DNP"
"D1","1","SMF9.0CA","D_TVS","acheron_Components:D_SOD-123_Bidirectional","Bidirectional transient-voltage-suppression diode","",""
"F1","1","ASMD1206-150","Polyfuse","Fuse:Fuse_1206_3216Metric","Resettable fuse, polymeric positive temperature coefficient","",""
"G1","1","Unified-Daughterboard-Logo","MountingHole","Unified-Daughterboard-Logo:Unified-Daughterboard-Logo.pretty","Mounting Hole without connection","",""
"G2","1","Unified-Daughterboard-Name","MountingHole","Unified-Daughterboard-Logo:Unified-Daughterboard-Name.pretty","Mounting Hole without connection","",""
"J1","1","TYPE-C-31-M12_13","TYPE-C-31-M12_13-acheronSymbols","acheron_Connectors:TYPE-C-31-M-12","","",""
"J2","1","SM04B-SRSS-TB(LF)(SN)","Conn_01x04","random-keyboard-parts:JST-SR-4","Generic connector, single row, 01x04, script generated (kicad-library-utils/schlib/autogen/connector/)","",""
"L1","1","60R@100MHz","L_Core_Ferrite-Device","Inductor_SMD:L_1206_3216Metric","","",""
"MH1, MH2, MH3, MH4","4","Mount-M2","Conn_01x01","random-keyboard-parts:Generic-Mounthole","Generic connector, single row, 01x01, script generated (kicad-library-utils/schlib/autogen/connector/)","",""
"R1, R2","2","5.1k","R_Small","Resistors_SMD:R_0603","Resistor, small symbol","",""
"U1","1","TPD4E05U06DQAR","TPD4E05U06DQAR-acheronSymbols","acheron_Components:USON-10_2.5x1.0mm_P0.5mm","","",""
